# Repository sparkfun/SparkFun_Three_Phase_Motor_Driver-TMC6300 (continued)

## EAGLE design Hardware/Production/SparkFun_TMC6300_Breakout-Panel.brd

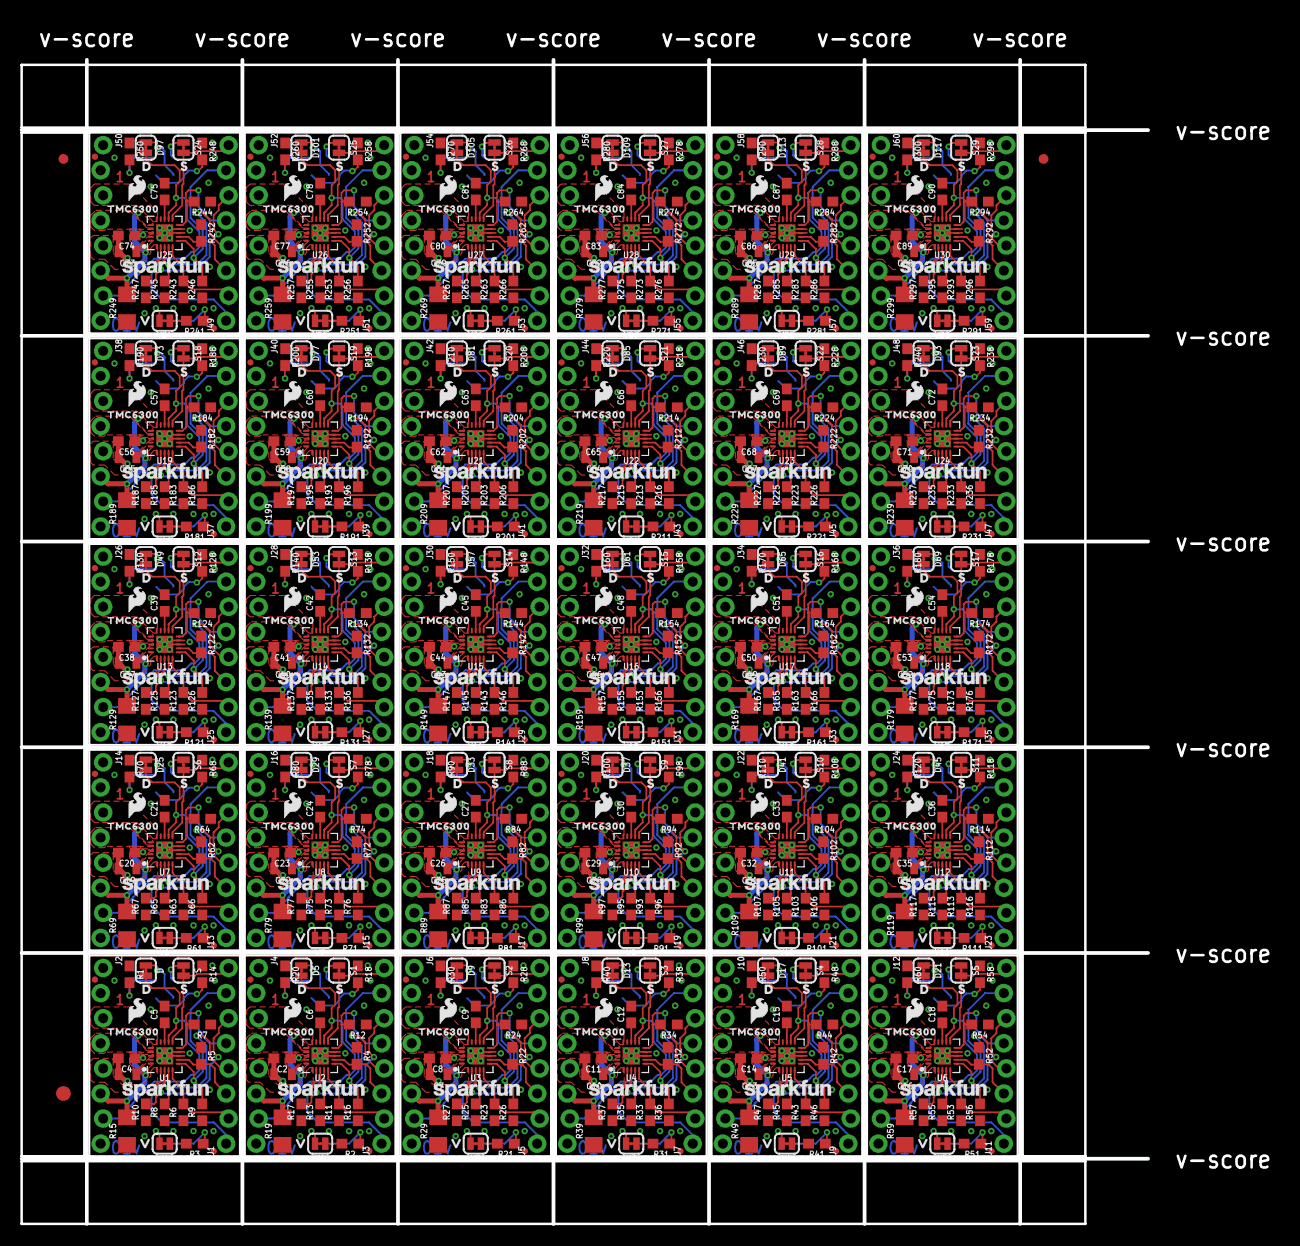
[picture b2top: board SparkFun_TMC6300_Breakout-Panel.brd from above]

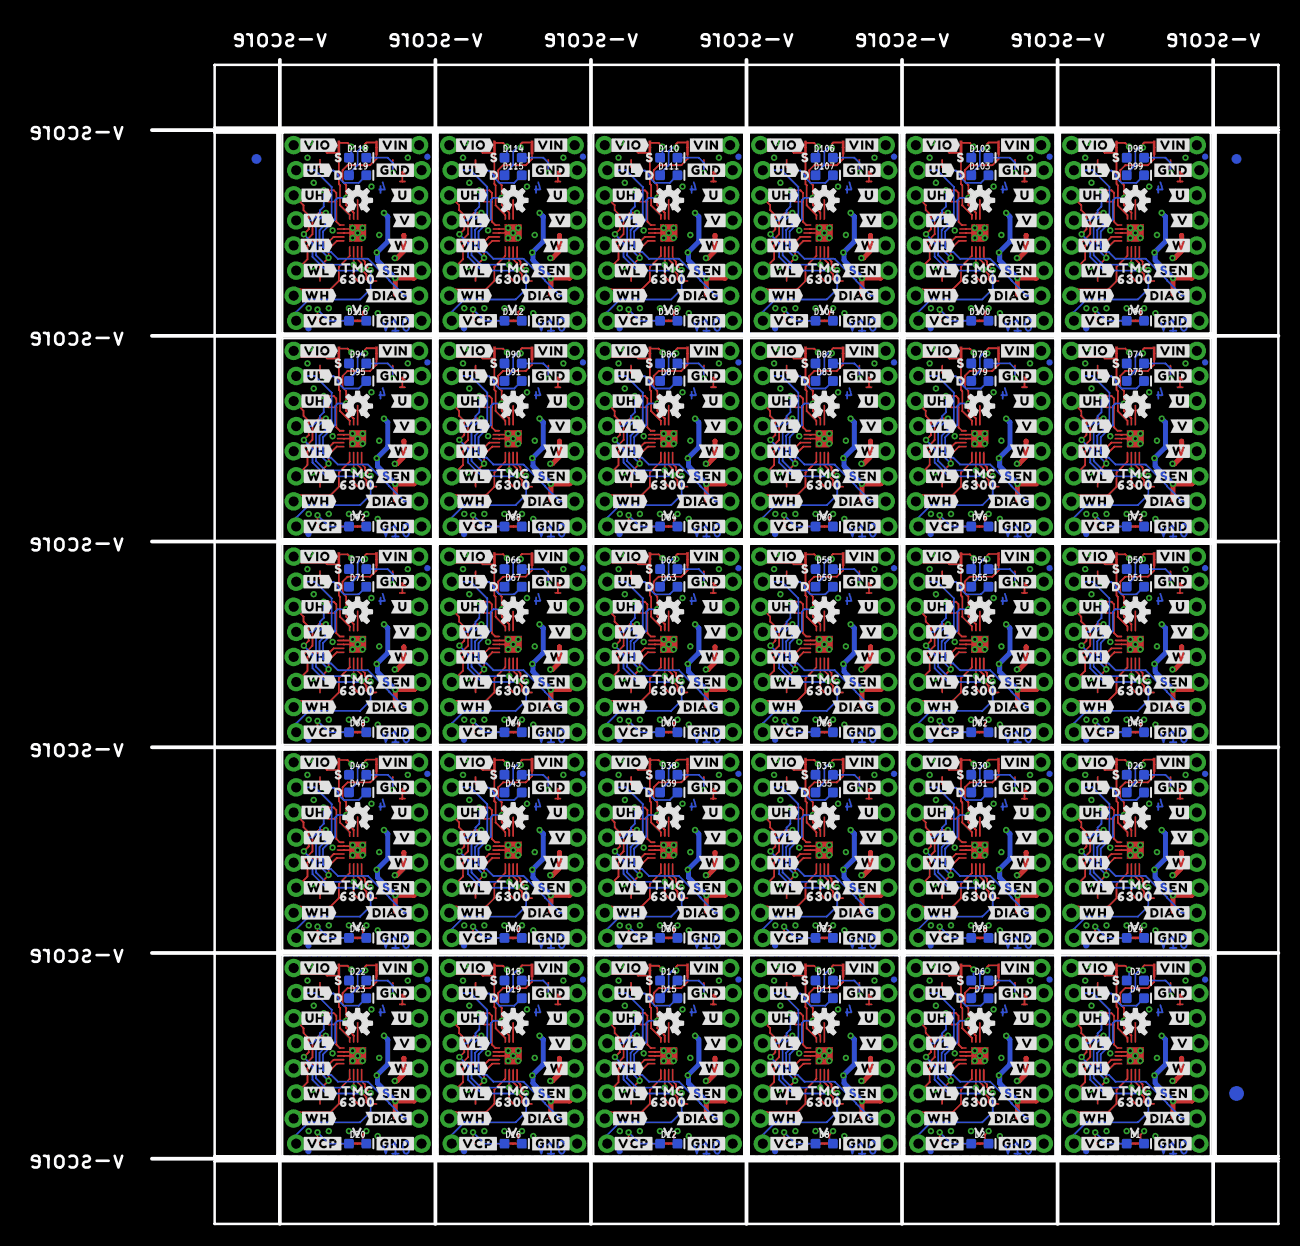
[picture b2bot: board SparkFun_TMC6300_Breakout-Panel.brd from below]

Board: 4 copper layers, 114.0 x 117.9 mm, 1626 parts (813 on the bottom side), 660 nets.

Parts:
C1, C3, C7, C10, C13, C16, C19, C22, C25, C28, C31, C34, C37, C40, C43, C46, C49, C52, C55, C58, C61, C64, C67, C70, C73, C76, C79, C82, C85, C88: 10uF; 0805
C2, C4, C5, C6, C8, C9, C11, C12, C14, C15, C17, C18, C20, C21, C23, C24, C26, C27, C29, C30, C32, C33, C35, C36, C38, C39, C41, C42, C44, C45, C47, C48, C50, C51, C53, C54, C56, C57, C59, C60, C62, C63, C65, C66, C68, C69, C71, C72, C74, C75, C77, C78, C80, C81, C83, C84, C86, C87, C89, C90: 0.1uF; 0603
D, D5, D9, D13, D17, D21, D25, D29, D33, D37, D41, D45, D49, D53, D57, D61, D65, D69, D73, D77, D81, D85, D89, D93, D97, D101, D105, D109, D113, D117: JUMPER-SMT_2_NC_TRACE_SILK; SMT-JUMPER_2_NC_TRACE_SILK
D1, D2, D8, D12, D16, D20, D24, D28, D32, D36, D40, D44, D48, D52, D56, D60, D64, D68, D72, D76, D80, D84, D88, D92, D96, D100, D104, D108, D112, D116: RED; LED-0603
D3, D6, D10, D14, D18, D22, D26, D30, D34, D38, D42, D46, D50, D54, D58, D62, D66, D70, D74, D78, D82, D86, D90, D94, D98, D102, D106, D110, D114, D118: BLUE; LED-0603
D4, D7, D11, D15, D19, D23, D27, D31, D35, D39, D43, D47, D51, D55, D59, D63, D67, D71, D75, D79, D83, D87, D91, D95, D99, D103, D107, D111, D115, D119: GREEN; LED-0603
E$1, E$2, E$3, E$4: FIDUCIAL-1X2
E$5, E$6: FIDUCIAL-1.5X3
FD1, FD2, FD3, FD4, FD5, FD6, FD7, FD8, FD9, FD10, FD11, FD12, FD13, FD14, FD15, FD16, FD17, FD18, FD19, FD20, FD21, FD22, FD23, FD24, FD25, FD26, FD27, FD28, FD29, FD30, FD31, FD32, FD33, FD34, FD35, FD36, FD37, FD38, FD39, FD40, FD41, FD42, FD43, FD44, FD45, FD46, FD47, FD48, FD49, FD50, FD51, FD52, FD53, FD54, FD55, FD56, FD57, FD58, FD59, FD60, FD61, FD62, FD63, FD64, FD65, FD66, FD67, FD68, FD69, FD70, FD71, FD72, FD73, FD74, FD75, FD76, FD77, FD78, FD79, FD80, FD81, FD82, FD83, FD84, FD85, FD86, FD87, FD88, FD89, FD90, FD91, FD92, FD93, FD94, FD95, FD96, FD97, FD98, FD99, FD100, FD101, FD102, FD103, FD104, FD105, FD106, FD107, FD108, FD109, FD110, FD111, FD112, FD113, FD114, FD115, FD116, FD117, FD118, FD119, FD120: FIDUCIALUFIDUCIAL; FIDUCIAL-MICRO
J1, J2, J3, J4, J5, J6, J7, J8, J9, J10, J11, J12, J13, J14, J15, J16, J17, J18, J19, J20, J21, J22, J23, J24, J25, J26, J27, J28, J29, J30, J31, J32, J33, J34, J35, J36, J37, J38, J39, J40, J41, J42, J43, J44, J45, J46, J47, J48, J49, J50, J51, J52, J53, J54, J55, J56, J57, J58, J59, J60: 1X08_LOCK_NO_SILK
LOGO1, LOGO3, LOGO7, LOGO10, LOGO13, LOGO16, LOGO19, LOGO22, LOGO25, LOGO28, LOGO31, LOGO34, LOGO37, LOGO40, LOGO43, LOGO46, LOGO49, LOGO52, LOGO55, LOGO58, LOGO61, LOGO64, LOGO67, LOGO70, LOGO73, LOGO76, LOGO79, LOGO82, LOGO85, LOGO88: SFE_LOGO_NAME.08_INCH; SFE_LOGO_NAME_.08
LOGO2, LOGO4, LOGO8, LOGO11, LOGO14, LOGO17, LOGO20, LOGO23, LOGO26, LOGO29, LOGO32, LOGO35, LOGO38, LOGO41, LOGO44, LOGO47, LOGO50, LOGO53, LOGO56, LOGO59, LOGO62, LOGO65, LOGO68, LOGO71, LOGO74, LOGO77, LOGO80, LOGO83, LOGO86, LOGO89: SFE_LOGO_FLAME.1_INCH; SFE_LOGO_FLAME_.1
LOGO5, LOGO6, LOGO9, LOGO12, LOGO15, LOGO18, LOGO21, LOGO24, LOGO27, LOGO30, LOGO33, LOGO36, LOGO39, LOGO42, LOGO45, LOGO48, LOGO51, LOGO54, LOGO57, LOGO60, LOGO63, LOGO66, LOGO69, LOGO72, LOGO75, LOGO78, LOGO81, LOGO84, LOGO87, LOGO90: OSHW-LOGOS; OSHW-LOGO-S
R1, R20, R30, R40, R50, R60, R70, R80, R90, R100, R110, R120, R130, R140, R150, R160, R170, R180, R190, R200, R210, R220, R230, R240, R250, R260, R270, R280, R290, R300: 2.2k; 0603
R2, R3, R21, R31, R41, R51, R61, R71, R81, R91, R101, R111, R121, R131, R141, R151, R161, R171, R181, R191, R201, R211, R221, R231, R241, R251, R261, R271, R281, R291: 1k; 0603
R4, R5, R6, R7, R8, R9, R10, R11, R12, R13, R16, R17, R22, R23, R24, R25, R26, R27, R32, R33, R34, R35, R36, R37, R42, R43, R44, R45, R46, R47, R52, R53, R54, R55, R56, R57, R62, R63, R64, R65, R66, R67, R72, R73, R74, R75, R76, R77, R82, R83, R84, R85, R86, R87, R92, R93, R94, R95, R96, R97, R102, R103, R104, R105, R106, R107, R112, R113, R114, R115, R116, R117, R122, R123, R124, R125, R126, R127, R132, R133, R134, R135, R136, R137, R142, R143, R144, R145, R146, R147, R152, R153, R154, R155, R156, R157, R162, R163, R164, R165, R166, R167, R172, R173, R174, R175, R176, R177, R182, R183, R184, R185, R186, R187, R192, R193, R194, R195, R196, R197, R202, R203, R204, R205, R206, R207, R212, R213, R214, R215, R216, R217, R222, R223, R224, R225, R226, R227, R232, R233, R234, R235, R236, R237, R242, R243, R244, R245, R246, R247, R252, R253, R254, R255, R256, R257, R262, R263, R264, R265, R266, R267, R272, R273, R274, R275, R276, R277, R282, R283, R284, R285, R286, R287, R292, R293, R294, R295, R296, R297: 100k; 0603
R14, R18, R28, R38, R48, R58, R68, R78, R88, R98, R108, R118, R128, R138, R148, R158, R168, R178, R188, R198, R208, R218, R228, R238, R248, R258, R268, R278, R288, R298: 330; 0603
R15, R19, R29, R39, R49, R59, R69, R79, R89, R99, R109, R119, R129, R139, R149, R159, R169, R179, R189, R199, R209, R219, R229, R239, R249, R259, R269, R279, R289, R299: 0.12; 1206
S, S1, S2, S3, S4, S5, S6, S7, S8, S9, S10, S11, S12, S13, S14, S15, S16, S17, S18, S19, S20, S21, S22, S23, S24, S25, S26, S27, S28, S29: JUMPER-SMT_2_NC_TRACE_SILK; SMT-JUMPER_2_NC_TRACE_SILK
U1, U2, U3, U4, U5, U6, U7, U8, U9, U10, U11, U12, U13, U14, U15, U16, U17, U18, U19, U20, U21, U22, U23, U24, U25, U26, U27, U28, U29, U30: TMC6300; QFN-20
U$1, U$5, U$28, U$38, U$51, U$63, U$76, U$88, U$101, U$113, U$126, U$138, U$151, U$163, U$176, U$188, U$201, U$213, U$226, U$238, U$251, U$263, U$276, U$288, U$301, U$313, U$326, U$338, U$351, U$363, U$376, U$388, U$401, U$413, U$426, U$438, U$451, U$463, U$476, U$488, U$501, U$513, U$526, U$538, U$551, U$563, U$576, U$588, U$601, U$613, U$626, U$638, U$651, U$663, U$676, U$688, U$701, U$713, U$726, U$738: #GND#1
U$2, U$48, U$73, U$98, U$123, U$148, U$173, U$198, U$223, U$248, U$273, U$298, U$323, U$348, U$373, U$398, U$423, U$448, U$473, U$498, U$523, U$548, U$573, U$598, U$623, U$648, U$673, U$698, U$723, U$748: #SEN#0
U$3, U$49, U$74, U$99, U$124, U$149, U$174, U$199, U$224, U$249, U$274, U$299, U$324, U$349, U$374, U$399, U$424, U$449, U$474, U$499, U$524, U$549, U$574, U$599, U$624, U$649, U$674, U$699, U$724, U$749: #DIAG#0
U$4, U$50, U$75, U$100, U$125, U$150, U$175, U$200, U$225, U$250, U$275, U$300, U$325, U$350, U$375, U$400, U$425, U$450, U$475, U$500, U$525, U$550, U$575, U$600, U$625, U$650, U$675, U$700, U$725, U$750: TMC630063003454
U$6, U$12, U$52, U$77, U$102, U$127, U$152, U$177, U$202, U$227, U$252, U$277, U$302, U$327, U$352, U$377, U$402, U$427, U$452, U$477, U$502, U$527, U$552, U$577, U$602, U$627, U$652, U$677, U$702, U$727: #VCP#0
U$7, U$13, U$53, U$78, U$103, U$128, U$153, U$178, U$203, U$228, U$253, U$278, U$303, U$328, U$353, U$378, U$403, U$428, U$453, U$478, U$503, U$528, U$553, U$578, U$603, U$628, U$653, U$678, U$703, U$728: #VIO#1
U$8, U$14, U$16, U$18, U$54, U$57, U$79, U$82, U$104, U$107, U$129, U$132, U$154, U$157, U$179, U$182, U$204, U$207, U$229, U$232, U$254, U$257, U$279, U$282, U$304, U$307, U$329, U$332, U$354, U$357, U$379, U$382, U$404, U$407, U$429, U$432, U$454, U$457, U$479, U$482, U$504, U$507, U$529, U$532, U$554, U$557, U$579, U$582, U$604, U$607, U$629, U$632, U$654, U$657, U$679, U$682, U$704, U$707, U$729, U$732: D0
U$9, U$39, U$64, U$89, U$114, U$139, U$164, U$189, U$214, U$239, U$264, U$289, U$314, U$339, U$364, U$389, U$414, U$439, U$464, U$489, U$514, U$539, U$564, U$589, U$614, U$639, U$664, U$689, U$714, U$739: #U#6
U$10, U$20, U$26, U$29, U$55, U$59, U$80, U$84, U$105, U$109, U$130, U$134, U$155, U$159, U$180, U$184, U$205, U$209, U$230, U$234, U$255, U$259, U$280, U$284, U$305, U$309, U$330, U$334, U$355, U$359, U$380, U$384, U$405, U$409, U$430, U$434, U$455, U$459, U$480, U$484, U$505, U$509, U$530, U$534, U$555, U$559, U$580, U$584, U$605, U$609, U$630, U$634, U$655, U$659, U$680, U$684, U$705, U$709, U$730, U$734: V2
U$11, U$17, U$19, U$27, U$56, U$58, U$81, U$83, U$106, U$108, U$131, U$133, U$156, U$158, U$181, U$183, U$206, U$208, U$231, U$233, U$256, U$258, U$281, U$283, U$306, U$308, U$331, U$333, U$356, U$358, U$381, U$383, U$406, U$408, U$431, U$433, U$456, U$458, U$481, U$483, U$506, U$508, U$531, U$533, U$556, U$558, U$581, U$583, U$606, U$608, U$631, U$633, U$656, U$658, U$681, U$683, U$706, U$708, U$731, U$733: S1
U$15, U$35, U$60, U$85, U$110, U$135, U$160, U$185, U$210, U$235, U$260, U$285, U$310, U$335, U$360, U$385, U$410, U$435, U$460, U$485, U$510, U$535, U$560, U$585, U$610, U$635, U$660, U$685, U$710, U$735: 63001
U$21, U$40, U$65, U$90, U$115, U$140, U$165, U$190, U$215, U$240, U$265, U$290, U$315, U$340, U$365, U$390, U$415, U$440, U$465, U$490, U$515, U$540, U$565, U$590, U$615, U$640, U$665, U$690, U$715, U$740: #UH#5
U$22, U$41, U$66, U$91, U$116, U$141, U$166, U$191, U$216, U$241, U$266, U$291, U$316, U$341, U$366, U$391, U$416, U$441, U$466, U$491, U$516, U$541, U$566, U$591, U$616, U$641, U$666, U$691, U$716, U$741: #UL#4
U$23, U$36, U$61, U$86, U$111, U$136, U$161, U$186, U$211, U$236, U$261, U$286, U$311, U$336, U$361, U$386, U$411, U$436, U$461, U$486, U$511, U$536, U$561, U$586, U$611, U$636, U$661, U$686, U$711, U$736: TMC0
U$24, U$37, U$62, U$87, U$112, U$137, U$162, U$187, U$212, U$237, U$262, U$287, U$312, U$337, U$362, U$387, U$412, U$437, U$462, U$487, U$512, U$537, U$562, U$587, U$612, U$637, U$662, U$687, U$712, U$737: #VIN#0
U$25, U$42, U$67, U$92, U$117, U$142, U$167, U$192, U$217, U$242, U$267, U$292, U$317, U$342, U$367, U$392, U$417, U$442, U$467, U$492, U$517, U$542, U$567, U$592, U$617, U$642, U$667, U$692, U$717, U$742: #V#7
U$30, U$43, U$68, U$93, U$118, U$143, U$168, U$193, U$218, U$243, U$268, U$293, U$318, U$343, U$368, U$393, U$418, U$443, U$468, U$493, U$518, U$543, U$568, U$593, U$618, U$643, U$668, U$693, U$718, U$743: #VH#2
U$31, U$44, U$69, U$94, U$119, U$144, U$169, U$194, U$219, U$244, U$269, U$294, U$319, U$344, U$369, U$394, U$419, U$444, U$469, U$494, U$519, U$544, U$569, U$594, U$619, U$644, U$669, U$694, U$719, U$744: #VL#3
U$32, U$45, U$70, U$95, U$120, U$145, U$170, U$195, U$220, U$245, U$270, U$295, U$320, U$345, U$370, U$395, U$420, U$445, U$470, U$495, U$520, U$545, U$570, U$595, U$620, U$645, U$670, U$695, U$720, U$745: #W#8
U$33, U$46, U$71, U$96, U$121, U$146, U$171, U$196, U$221, U$246, U$271, U$296, U$321, U$346, U$371, U$396, U$421, U$446, U$471, U$496, U$521, U$546, U$571, U$596, U$621, U$646, U$671, U$696, U$721, U$746: #WH#1
U$34, U$47, U$72, U$97, U$122, U$147, U$172, U$197, U$222, U$247, U$272, U$297, U$322, U$347, U$372, U$397, U$422, U$447, U$472, U$497, U$522, U$547, U$572, U$597, U$622, U$647, U$672, U$697, U$722, U$747: #WL#0
V, V1, V2, V3, V4, V5, V6, V7, V8, V9, V10, V11, V12, V13, V14, V15, V16, V17, V18, V19, V20, V21, V22, V23, V24, V25, V26, V27, V28, V29: JUMPER-SMT_2_NC_TRACE_SILK; SMT-JUMPER_2_NC_TRACE_SILK

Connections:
DIAG: D.2, J2.7, U1.12
DIAG1: D5.2, J4.7, U2.12
DIAG2: D9.2, J6.7, U3.12
DIAG3: D13.2, J8.7, U4.12
DIAG4: D17.2, J10.7, U5.12
DIAG5: D21.2, J12.7, U6.12
DIAG6: D25.2, J14.7, U7.12
DIAG7: D29.2, J16.7, U8.12
DIAG8: D33.2, J18.7, U9.12
DIAG9: D37.2, J20.7, U10.12
DIAG10: D41.2, J22.7, U11.12
DIAG11: D45.2, J24.7, U12.12
DIAG12: D49.2, J26.7, U13.12
DIAG13: D53.2, J28.7, U14.12
DIAG14: D57.2, J30.7, U15.12
DIAG15: D61.2, J32.7, U16.12
DIAG16: D65.2, J34.7, U17.12
DIAG17: D69.2, J36.7, U18.12
DIAG18: D73.2, J38.7, U19.12
DIAG19: D77.2, J40.7, U20.12
DIAG20: D81.2, J42.7, U21.12
DIAG21: D85.2, J44.7, U22.12
DIAG22: D89.2, J46.7, U23.12
DIAG23: D93.2, J48.7, U24.12
DIAG24: D97.2, J50.7, U25.12
DIAG25: D101.2, J52.7, U26.12
DIAG26: D105.2, J54.7, U27.12
DIAG27: D109.2, J56.7, U28.12
DIAG28: D113.2, J58.7, U29.12
DIAG29: D117.2, J60.7, U30.12
GND: C3.2, C4.2, C5.2, D1.C, J2.2, J2.8, R1.1, R5.1, R6.1, R7.1, R8.1, R9.1, R10.1, R14.1, R15.1, U1.8, U1.9, U1.14, U1.PAD
GND1: C1.2, C2.2, C6.2, D2.C, J4.2, J4.8, R4.1, R11.1, R12.1, R13.1, R16.1, R17.1, R18.1, R19.1, R20.1, U2.8, U2.9, U2.14, U2.PAD
GND2: C7.2, C8.2, C9.2, D8.C, J6.2, J6.8, R22.1, R23.1, R24.1, R25.1, R26.1, R27.1, R28.1, R29.1, R30.1, U3.8, U3.9, U3.14, U3.PAD
GND3: C10.2, C11.2, C12.2, D12.C, J8.2, J8.8, R32.1, R33.1, R34.1, R35.1, R36.1, R37.1, R38.1, R39.1, R40.1, U4.8, U4.9, U4.14, U4.PAD
GND4: C13.2, C14.2, C15.2, D16.C, J10.2, J10.8, R42.1, R43.1, R44.1, R45.1, R46.1, R47.1, R48.1, R49.1, R50.1, U5.8, U5.9, U5.14, U5.PAD
GND5: C16.2, C17.2, C18.2, D20.C, J12.2, J12.8, R52.1, R53.1, R54.1, R55.1, R56.1, R57.1, R58.1, R59.1, R60.1, U6.8, U6.9, U6.14, U6.PAD
GND6: C19.2, C20.2, C21.2, D24.C, J14.2, J14.8, R62.1, R63.1, R64.1, R65.1, R66.1, R67.1, R68.1, R69.1, R70.1, U7.8, U7.9, U7.14, U7.PAD
GND7: C22.2, C23.2, C24.2, D28.C, J16.2, J16.8, R72.1, R73.1, R74.1, R75.1, R76.1, R77.1, R78.1, R79.1, R80.1, U8.8, U8.9, U8.14, U8.PAD
GND8: C25.2, C26.2, C27.2, D32.C, J18.2, J18.8, R82.1, R83.1, R84.1, R85.1, R86.1, R87.1, R88.1, R89.1, R90.1, U9.8, U9.9, U9.14, U9.PAD
GND9: C28.2, C29.2, C30.2, D36.C, J20.2, J20.8, R92.1, R93.1, R94.1, R95.1, R96.1, R97.1, R98.1, R99.1, R100.1, U10.8, U10.9, U10.14, U10.PAD
GND10: C31.2, C32.2, C33.2, D40.C, J22.2, J22.8, R102.1, R103.1, R104.1, R105.1, R106.1, R107.1, R108.1, R109.1, R110.1, U11.8, U11.9, U11.14, U11.PAD
GND11: C34.2, C35.2, C36.2, D44.C, J24.2, J24.8, R112.1, R113.1, R114.1, R115.1, R116.1, R117.1, R118.1, R119.1, R120.1, U12.8, U12.9, U12.14, U12.PAD
GND12: C37.2, C38.2, C39.2, D48.C, J26.2, J26.8, R122.1, R123.1, R124.1, R125.1, R126.1, R127.1, R128.1, R129.1, R130.1, U13.8, U13.9, U13.14, U13.PAD
GND13: C40.2, C41.2, C42.2, D52.C, J28.2, J28.8, R132.1, R133.1, R134.1, R135.1, R136.1, R137.1, R138.1, R139.1, R140.1, U14.8, U14.9, U14.14, U14.PAD
GND14: C43.2, C44.2, C45.2, D56.C, J30.2, J30.8, R142.1, R143.1, R144.1, R145.1, R146.1, R147.1, R148.1, R149.1, R150.1, U15.8, U15.9, U15.14, U15.PAD
GND15: C46.2, C47.2, C48.2, D60.C, J32.2, J32.8, R152.1, R153.1, R154.1, R155.1, R156.1, R157.1, R158.1, R159.1, R160.1, U16.8, U16.9, U16.14, U16.PAD
GND16: C49.2, C50.2, C51.2, D64.C, J34.2, J34.8, R162.1, R163.1, R164.1, R165.1, R166.1, R167.1, R168.1, R169.1, R170.1, U17.8, U17.9, U17.14, U17.PAD
GND17: C52.2, C53.2, C54.2, D68.C, J36.2, J36.8, R172.1, R173.1, R174.1, R175.1, R176.1, R177.1, R178.1, R179.1, R180.1, U18.8, U18.9, U18.14, U18.PAD
GND18: C55.2, C56.2, C57.2, D72.C, J38.2, J38.8, R182.1, R183.1, R184.1, R185.1, R186.1, R187.1, R188.1, R189.1, R190.1, U19.8, U19.9, U19.14, U19.PAD
GND19: C58.2, C59.2, C60.2, D76.C, J40.2, J40.8, R192.1, R193.1, R194.1, R195.1, R196.1, R197.1, R198.1, R199.1, R200.1, U20.8, U20.9, U20.14, U20.PAD
GND20: C61.2, C62.2, C63.2, D80.C, J42.2, J42.8, R202.1, R203.1, R204.1, R205.1, R206.1, R207.1, R208.1, R209.1, R210.1, U21.8, U21.9, U21.14, U21.PAD
GND21: C64.2, C65.2, C66.2, D84.C, J44.2, J44.8, R212.1, R213.1, R214.1, R215.1, R216.1, R217.1, R218.1, R219.1, R220.1, U22.8, U22.9, U22.14, U22.PAD
GND22: C67.2, C68.2, C69.2, D88.C, J46.2, J46.8, R222.1, R223.1, R224.1, R225.1, R226.1, R227.1, R228.1, R229.1, R230.1, U23.8, U23.9, U23.14, U23.PAD
GND23: C70.2, C71.2, C72.2, D92.C, J48.2, J48.8, R232.1, R233.1, R234.1, R235.1, R236.1, R237.1, R238.1, R239.1, R240.1, U24.8, U24.9, U24.14, U24.PAD
GND24: C73.2, C74.2, C75.2, D96.C, J50.2, J50.8, R242.1, R243.1, R244.1, R245.1, R246.1, R247.1, R248.1, R249.1, R250.1, U25.8, U25.9, U25.14, U25.PAD
GND25: C76.2, C77.2, C78.2, D100.C, J52.2, J52.8, R252.1, R253.1, R254.1, R255.1, R256.1, R257.1, R258.1, R259.1, R260.1, U26.8, U26.9, U26.14, U26.PAD
GND26: C79.2, C80.2, C81.2, D104.C, J54.2, J54.8, R262.1, R263.1, R264.1, R265.1, R266.1, R267.1, R268.1, R269.1, R270.1, U27.8, U27.9, U27.14, U27.PAD
GND27: C82.2, C83.2, C84.2, D108.C, J56.2, J56.8, R272.1, R273.1, R274.1, R275.1, R276.1, R277.1, R278.1, R279.1, R280.1, U28.8, U28.9, U28.14, U28.PAD
GND28: C85.2, C86.2, C87.2, D112.C, J58.2, J58.8, R282.1, R283.1, R284.1, R285.1, R286.1, R287.1, R288.1, R289.1, R290.1, U29.8, U29.9, U29.14, U29.PAD
GND29: C88.2, C89.2, C90.2, D116.C, J60.2, J60.8, R292.1, R293.1, R294.1, R295.1, R296.1, R297.1, R298.1, R299.1, R300.1, U30.8, U30.9, U30.14, U30.PAD
unnamed: R3.2, V.1
unnamed: R2.2, V1.1
unnamed: D2.A, R2.1
unnamed: D1.A, R3.1
unnamed: D3.A, S.1
unnamed: C5.1, U1.13
unnamed: C6.1, U2.13
unnamed: D5.1, D7.A
unnamed: D.1, D4.A
unnamed: D3.C, R1.2
unnamed: D6.A, S1.1
unnamed: D4.C, R14.2
unnamed: D7.C, R18.2
unnamed: D6.C, R20.2
unnamed: R21.2, V2.1
unnamed: D8.A, R21.1
unnamed: C9.1, U3.13
unnamed: D9.1, D11.A
unnamed: D10.A, S2.1
unnamed: D11.C, R28.2
unnamed: D10.C, R30.2
unnamed: R31.2, V3.1
unnamed: D12.A, R31.1
unnamed: C12.1, U4.13
unnamed: D13.1, D15.A
unnamed: D14.A, S3.1
unnamed: D15.C, R38.2
unnamed: D14.C, R40.2
unnamed: R41.2, V4.1
unnamed: D16.A, R41.1
unnamed: C15.1, U5.13
unnamed: D17.1, D19.A
unnamed: D18.A, S4.1
unnamed: D19.C, R48.2
unnamed: D18.C, R50.2
unnamed: R51.2, V5.1
unnamed: D20.A, R51.1
unnamed: C18.1, U6.13
unnamed: D21.1, D23.A
unnamed: D22.A, S5.1
unnamed: D23.C, R58.2
unnamed: D22.C, R60.2
unnamed: R61.2, V6.1
unnamed: D24.A, R61.1
unnamed: C21.1, U7.13
unnamed: D25.1, D27.A
unnamed: D26.A, S6.1
unnamed: D27.C, R68.2
unnamed: D26.C, R70.2
unnamed: R71.2, V7.1
unnamed: D28.A, R71.1
unnamed: C24.1, U8.13
unnamed: D29.1, D31.A
unnamed: D30.A, S7.1
unnamed: D31.C, R78.2
unnamed: D30.C, R80.2
unnamed: R81.2, V8.1
unnamed: D32.A, R81.1
unnamed: C27.1, U9.13
unnamed: D33.1, D35.A
unnamed: D34.A, S8.1
unnamed: D35.C, R88.2
unnamed: D34.C, R90.2
unnamed: R91.2, V9.1
unnamed: D36.A, R91.1
unnamed: C30.1, U10.13
unnamed: D37.1, D39.A
unnamed: D38.A, S9.1
unnamed: D39.C, R98.2
unnamed: D38.C, R100.2
unnamed: R101.2, V10.1
unnamed: D40.A, R101.1
unnamed: C33.1, U11.13
unnamed: D41.1, D43.A
unnamed: D42.A, S10.1
unnamed: D43.C, R108.2
unnamed: D42.C, R110.2
unnamed: R111.2, V11.1
unnamed: D44.A, R111.1
unnamed: C36.1, U12.13
unnamed: D45.1, D47.A
unnamed: D46.A, S11.1
unnamed: D47.C, R118.2
unnamed: D46.C, R120.2
unnamed: R121.2, V12.1
unnamed: D48.A, R121.1
unnamed: C39.1, U13.13
unnamed: D49.1, D51.A
unnamed: D50.A, S12.1
unnamed: D51.C, R128.2
unnamed: D50.C, R130.2
unnamed: R131.2, V13.1
unnamed: D52.A, R131.1
unnamed: C42.1, U14.13
unnamed: D53.1, D55.A
unnamed: D54.A, S13.1
unnamed: D55.C, R138.2
unnamed: D54.C, R140.2
unnamed: R141.2, V14.1
unnamed: D56.A, R141.1
unnamed: C45.1, U15.13
unnamed: D57.1, D59.A
unnamed: D58.A, S14.1
unnamed: D59.C, R148.2
unnamed: D58.C, R150.2
unnamed: R151.2, V15.1
unnamed: D60.A, R151.1
unnamed: C48.1, U16.13
unnamed: D61.1, D63.A
unnamed: D62.A, S15.1
unnamed: D63.C, R158.2
unnamed: D62.C, R160.2
unnamed: R161.2, V16.1
unnamed: D64.A, R161.1
unnamed: C51.1, U17.13
unnamed: D65.1, D67.A
unnamed: D66.A, S16.1
unnamed: D67.C, R168.2
unnamed: D66.C, R170.2
unnamed: R171.2, V17.1
unnamed: D68.A, R171.1
unnamed: C54.1, U18.13
unnamed: D69.1, D71.A
unnamed: D70.A, S17.1
unnamed: D71.C, R178.2
unnamed: D70.C, R180.2
unnamed: R181.2, V18.1
unnamed: D72.A, R181.1
unnamed: C57.1, U19.13
unnamed: D73.1, D75.A
unnamed: D74.A, S18.1
unnamed: D75.C, R188.2
unnamed: D74.C, R190.2
unnamed: R191.2, V19.1
unnamed: D76.A, R191.1
unnamed: C60.1, U20.13
unnamed: D77.1, D79.A
unnamed: D78.A, S19.1
unnamed: D79.C, R198.2
unnamed: D78.C, R200.2
unnamed: R201.2, V20.1
unnamed: D80.A, R201.1
unnamed: C63.1, U21.13
unnamed: D81.1, D83.A
unnamed: D82.A, S20.1
unnamed: D83.C, R208.2
unnamed: D82.C, R210.2
unnamed: R211.2, V21.1
unnamed: D84.A, R211.1
unnamed: C66.1, U22.13
unnamed: D85.1, D87.A
unnamed: D86.A, S21.1
unnamed: D87.C, R218.2
unnamed: D86.C, R220.2
unnamed: R221.2, V22.1
unnamed: D88.A, R221.1
unnamed: C69.1, U23.13
unnamed: D89.1, D91.A
unnamed: D90.A, S22.1
unnamed: D91.C, R228.2
unnamed: D90.C, R230.2
unnamed: R231.2, V23.1
unnamed: D92.A, R231.1
unnamed: C72.1, U24.13
unnamed: D93.1, D95.A
unnamed: D94.A, S23.1
unnamed: D95.C, R238.2
unnamed: D94.C, R240.2
unnamed: R241.2, V24.1
unnamed: D96.A, R241.1
unnamed: C75.1, U25.13
unnamed: D97.1, D99.A
unnamed: D98.A, S24.1
unnamed: D99.C, R248.2
unnamed: D98.C, R250.2
unnamed: R251.2, V25.1
unnamed: D100.A, R251.1
unnamed: C78.1, U26.13
unnamed: D101.1, D103.A
unnamed: D102.A, S25.1
unnamed: D103.C, R258.2
unnamed: D102.C, R260.2
unnamed: R261.2, V26.1
unnamed: D104.A, R261.1
unnamed: C81.1, U27.13
unnamed: D105.1, D107.A
unnamed: D106.A, S26.1
unnamed: D107.C, R268.2
unnamed: D106.C, R270.2
unnamed: R271.2, V27.1
unnamed: D108.A, R271.1
unnamed: C84.1, U28.13
unnamed: D109.1, D111.A
unnamed: D110.A, S27.1
unnamed: D111.C, R278.2
unnamed: D110.C, R280.2
unnamed: R281.2, V28.1
unnamed: D112.A, R281.1
unnamed: C87.1, U29.13
unnamed: D113.1, D115.A
unnamed: D114.A, S28.1
unnamed: D115.C, R288.2
unnamed: D114.C, R290.2
unnamed: R291.2, V29.1
unnamed: D116.A, R291.1
unnamed: C90.1, U30.13
unnamed: D117.1, D119.A
unnamed: D118.A, S29.1
unnamed: D119.C, R298.2
unnamed: D118.C, R300.2
SENSE: J2.6, R15.2, U1.16, U1.20
SENSE1: J4.6, R19.2, U2.16, U2.20
SENSE2: J6.6, R29.2, U3.16, U3.20
SENSE3: J8.6, R39.2, U4.16, U4.20
SENSE4: J10.6, R49.2, U5.16, U5.20
SENSE5: J12.6, R59.2, U6.16, U6.20
SENSE6: J14.6, R69.2, U7.16, U7.20
SENSE7: J16.6, R79.2, U8.16, U8.20
SENSE8: J18.6, R89.2, U9.16, U9.20
SENSE9: J20.6, R99.2, U10.16, U10.20
SENSE10: J22.6, R109.2, U11.16, U11.20
SENSE11: J24.6, R119.2, U12.16, U12.20
SENSE12: J26.6, R129.2, U13.16, U13.20
SENSE13: J28.6, R139.2, U14.16, U14.20
SENSE14: J30.6, R149.2, U15.16, U15.20
SENSE15: J32.6, R159.2, U16.16, U16.20
SENSE16: J34.6, R169.2, U17.16, U17.20
SENSE17: J36.6, R179.2, U18.16, U18.20
SENSE18: J38.6, R189.2, U19.16, U19.20
SENSE19: J40.6, R199.2, U20.16, U20.20
SENSE20: J42.6, R209.2, U21.16, U21.20
SENSE21: J44.6, R219.2, U22.16, U22.20
SENSE22: J46.6, R229.2, U23.16, U23.20
SENSE23: J48.6, R239.2, U24.16, U24.20
SENSE24: J50.6, R249.2, U25.16, U25.20
SENSE25: J52.6, R259.2, U26.16, U26.20
SENSE26: J54.6, R269.2, U27.16, U27.20
SENSE27: J56.6, R279.2, U28.16, U28.20
SENSE28: J58.6, R289.2, U29.16, U29.20
SENSE29: J60.6, R299.2, U30.16, U30.20
U: J2.3, U1.15
U1: J4.3, U2.15
U2: J6.3, U3.15
U3: J8.3, U4.15
U4: J10.3, U5.15
U5: J12.3, U6.15
U6: J14.3, U7.15
U7: J16.3, U8.15
U8: J18.3, U9.15
U9: J20.3, U10.15
U10: J22.3, U11.15
U11: J24.3, U12.15
U12: J26.3, U13.15
U13: J28.3, U14.15
U14: J30.3, U15.15
U15: J32.3, U16.15
U16: J34.3, U17.15
U17: J36.3, U18.15
U18: J38.3, U19.15
U19: J40.3, U20.15
U20: J42.3, U21.15
U21: J44.3, U22.15
U22: J46.3, U23.15
U23: J48.3, U24.15
U24: J50.3, U25.15
U25: J52.3, U26.15
U26: J54.3, U27.15
U27: J56.3, U28.15
U28: J58.3, U29.15
U29: J60.3, U30.15
UH: J1.6, R10.2, U1.3
UH1: J3.6, R17.2, U2.3
UH2: J5.6, R27.2, U3.3
UH3: J7.6, R37.2, U4.3
UH4: J9.6, R47.2, U5.3
UH5: J11.6, R57.2, U6.3
UH6: J13.6, R67.2, U7.3
UH7: J15.6, R77.2, U8.3
UH8: J17.6, R87.2, U9.3
UH9: J19.6, R97.2, U10.3
UH10: J21.6, R107.2, U11.3
UH11: J23.6, R117.2, U12.3
UH12: J25.6, R127.2, U13.3
UH13: J27.6, R137.2, U14.3
UH14: J29.6, R147.2, U15.3
UH15: J31.6, R157.2, U16.3
UH16: J33.6, R167.2, U17.3
UH17: J35.6, R177.2, U18.3
UH18: J37.6, R187.2, U19.3
UH19: J39.6, R197.2, U20.3
UH20: J41.6, R207.2, U21.3
UH21: J43.6, R217.2, U22.3
UH22: J45.6, R227.2, U23.3
UH23: J47.6, R237.2, U24.3
UH24: J49.6, R247.2, U25.3
UH25: J51.6, R257.2, U26.3
UH26: J53.6, R267.2, U27.3
UH27: J55.6, R277.2, U28.3
UH28: J57.6, R287.2, U29.3
UH29: J59.6, R297.2, U30.3
UL: J1.7, R9.2, U1.6
UL1: J3.7, R16.2, U2.6
UL2: J5.7, R26.2, U3.6
UL3: J7.7, R36.2, U4.6
UL4: J9.7, R46.2, U5.6
UL5: J11.7, R56.2, U6.6
UL6: J13.7, R66.2, U7.6
UL7: J15.7, R76.2, U8.6
UL8: J17.7, R86.2, U9.6
UL9: J19.7, R96.2, U10.6
UL10: J21.7, R106.2, U11.6
UL11: J23.7, R116.2, U12.6
UL12: J25.7, R126.2, U13.6
UL13: J27.7, R136.2, U14.6
UL14: J29.7, R146.2, U15.6
UL15: J31.7, R156.2, U16.6
UL16: J33.7, R166.2, U17.6
UL17: J35.7, R176.2, U18.6
UL18: J37.7, R186.2, U19.6
UL19: J39.7, R196.2, U20.6
UL20: J41.7, R206.2, U21.6
UL21: J43.7, R216.2, U22.6
UL22: J45.7, R226.2, U23.6
UL23: J47.7, R236.2, U24.6
UL24: J49.7, R246.2, U25.6
UL25: J51.7, R256.2, U26.6
UL26: J53.7, R266.2, U27.6
UL27: J55.7, R276.2, U28.6
UL28: J57.7, R286.2, U29.6
UL29: J59.7, R296.2, U30.6
V: J2.4, U1.17
V1: J4.4, U2.17
V2: J6.4, U3.17
V3: J8.4, U4.17
V4: J10.4, U5.17
V5: J12.4, U6.17
V6: J14.4, U7.17
V7: J16.4, U8.17
V8: J18.4, U9.17
V9: J20.4, U10.17
V10: J22.4, U11.17
V11: J24.4, U12.17
V12: J26.4, U13.17
V13: J28.4, U14.17
V14: J30.4, U15.17
V15: J32.4, U16.17
V16: J34.4, U17.17
V17: J36.4, U18.17
V18: J38.4, U19.17
V19: J40.4, U20.17
V20: J42.4, U21.17
V21: J44.4, U22.17
V22: J46.4, U23.17
V23: J48.4, U24.17
V24: J50.4, U25.17
V25: J52.4, U26.17
V26: J54.4, U27.17
V27: J56.4, U28.17
V28: J58.4, U29.17
V29: J60.4, U30.17
VCP: J1.1, U1.2
VCP1: J3.1, U2.2
VCP2: J5.1, U3.2
VCP3: J7.1, U4.2
VCP4: J9.1, U5.2
VCP5: J11.1, U6.2
VCP6: J13.1, U7.2
VCP7: J15.1, U8.2
VCP8: J17.1, U9.2
VCP9: J19.1, U10.2
VCP10: J21.1, U11.2
VCP11: J23.1, U12.2
VCP12: J25.1, U13.2
VCP13: J27.1, U14.2
VCP14: J29.1, U15.2
VCP15: J31.1, U16.2
VCP16: J33.1, U17.2
VCP17: J35.1, U18.2
VCP18: J37.1, U19.2
VCP19: J39.1, U20.2
VCP20: J41.1, U21.2
VCP21: J43.1, U22.2
VCP22: J45.1, U23.2
VCP23: J47.1, U24.2
VCP24: J49.1, U25.2
VCP25: J51.1, U26.2
VCP26: J53.1, U27.2
VCP27: J55.1, U28.2
VCP28: J57.1, U29.2
VCP29: J59.1, U30.2
VH: J1.4, R8.2, U1.4
VH1: J3.4, R13.2, U2.4
VH2: J5.4, R25.2, U3.4
VH3: J7.4, R35.2, U4.4
VH4: J9.4, R45.2, U5.4
VH5: J11.4, R55.2, U6.4
VH6: J13.4, R65.2, U7.4
VH7: J15.4, R75.2, U8.4
VH8: J17.4, R85.2, U9.4
VH9: J19.4, R95.2, U10.4
VH10: J21.4, R105.2, U11.4
VH11: J23.4, R115.2, U12.4
VH12: J25.4, R125.2, U13.4
VH13: J27.4, R135.2, U14.4
VH14: J29.4, R145.2, U15.4
VH15: J31.4, R155.2, U16.4
VH16: J33.4, R165.2, U17.4
VH17: J35.4, R175.2, U18.4
VH18: J37.4, R185.2, U19.4
VH19: J39.4, R195.2, U20.4
VH20: J41.4, R205.2, U21.4
VH21: J43.4, R215.2, U22.4
VH22: J45.4, R225.2, U23.4
VH23: J47.4, R235.2, U24.4
VH24: J49.4, R245.2, U25.4
VH25: J51.4, R255.2, U26.4
VH26: J53.4, R265.2, U27.4
VH27: J55.4, R275.2, U28.4
VH28: J57.4, R285.2, U29.4
VH29: J59.4, R295.2, U30.4
VIN: C3.1, C4.1, J2.1, U1.18, V.2
VIN1: C1.1, C2.1, J4.1, U2.18, V1.2
VIN2: C7.1, C8.1, J6.1, U3.18, V2.2
VIN3: C10.1, C11.1, J8.1, U4.18, V3.2
VIN4: C13.1, C14.1, J10.1, U5.18, V4.2
VIN5: C16.1, C17.1, J12.1, U6.18, V5.2
VIN6: C19.1, C20.1, J14.1, U7.18, V6.2
VIN7: C22.1, C23.1, J16.1, U8.18, V7.2
VIN8: C25.1, C26.1, J18.1, U9.18, V8.2
VIN9: C28.1, C29.1, J20.1, U10.18, V9.2
VIN10: C31.1, C32.1, J22.1, U11.18, V10.2
VIN11: C34.1, C35.1, J24.1, U12.18, V11.2
VIN12: C37.1, C38.1, J26.1, U13.18, V12.2
VIN13: C40.1, C41.1, J28.1, U14.18, V13.2
VIN14: C43.1, C44.1, J30.1, U15.18, V14.2
VIN15: C46.1, C47.1, J32.1, U16.18, V15.2
VIN16: C49.1, C50.1, J34.1, U17.18, V16.2
VIN17: C52.1, C53.1, J36.1, U18.18, V17.2
VIN18: C55.1, C56.1, J38.1, U19.18, V18.2
VIN19: C58.1, C59.1, J40.1, U20.18, V19.2
VIN20: C61.1, C62.1, J42.1, U21.18, V20.2
VIN21: C64.1, C65.1, J44.1, U22.18, V21.2
VIN22: C67.1, C68.1, J46.1, U23.18, V22.2
VIN23: C70.1, C71.1, J48.1, U24.18, V23.2
VIN24: C73.1, C74.1, J50.1, U25.18, V24.2
VIN25: C76.1, C77.1, J52.1, U26.18, V25.2
VIN26: C79.1, C80.1, J54.1, U27.18, V26.2
VIN27: C82.1, C83.1, J56.1, U28.18, V27.2
VIN28: C85.1, C86.1, J58.1, U29.18, V28.2
VIN29: C88.1, C89.1, J60.1, U30.18, V29.2
VIO/!STDBY!: J1.8, S.2, U1.11
VIO/!STDBY!1: J3.8, S1.2, U2.11
VIO/!STDBY!2: J5.8, S2.2, U3.11
VIO/!STDBY!3: J7.8, S3.2, U4.11
VIO/!STDBY!4: J9.8, S4.2, U5.11
VIO/!STDBY!5: J11.8, S5.2, U6.11
VIO/!STDBY!6: J13.8, S6.2, U7.11
VIO/!STDBY!7: J15.8, S7.2, U8.11
VIO/!STDBY!8: J17.8, S8.2, U9.11
VIO/!STDBY!9: J19.8, S9.2, U10.11
VIO/!STDBY!10: J21.8, S10.2, U11.11
VIO/!STDBY!11: J23.8, S11.2, U12.11
VIO/!STDBY!12: J25.8, S12.2, U13.11
VIO/!STDBY!13: J27.8, S13.2, U14.11
VIO/!STDBY!14: J29.8, S14.2, U15.11
VIO/!STDBY!15: J31.8, S15.2, U16.11
VIO/!STDBY!16: J33.8, S16.2, U17.11
VIO/!STDBY!17: J35.8, S17.2, U18.11
VIO/!STDBY!18: J37.8, S18.2, U19.11
VIO/!STDBY!19: J39.8, S19.2, U20.11
VIO/!STDBY!20: J41.8, S20.2, U21.11
VIO/!STDBY!21: J43.8, S21.2, U22.11
VIO/!STDBY!22: J45.8, S22.2, U23.11
VIO/!STDBY!23: J47.8, S23.2, U24.11
VIO/!STDBY!24: J49.8, S24.2, U25.11
VIO/!STDBY!25: J51.8, S25.2, U26.11
VIO/!STDBY!26: J53.8, S26.2, U27.11
VIO/!STDBY!27: J55.8, S27.2, U28.11
VIO/!STDBY!28: J57.8, S28.2, U29.11
VIO/!STDBY!29: J59.8, S29.2, U30.11
VL: J1.5, R7.2, U1.10
VL1: J3.5, R12.2, U2.10
VL2: J5.5, R24.2, U3.10
VL3: J7.5, R34.2, U4.10
VL4: J9.5, R44.2, U5.10
VL5: J11.5, R54.2, U6.10
VL6: J13.5, R64.2, U7.10
VL7: J15.5, R74.2, U8.10
VL8: J17.5, R84.2, U9.10
VL9: J19.5, R94.2, U10.10
VL10: J21.5, R104.2, U11.10
VL11: J23.5, R114.2, U12.10
VL12: J25.5, R124.2, U13.10
VL13: J27.5, R134.2, U14.10
VL14: J29.5, R144.2, U15.10
VL15: J31.5, R154.2, U16.10
VL16: J33.5, R164.2, U17.10
VL17: J35.5, R174.2, U18.10
VL18: J37.5, R184.2, U19.10
VL19: J39.5, R194.2, U20.10
VL20: J41.5, R204.2, U21.10
VL21: J43.5, R214.2, U22.10
VL22: J45.5, R224.2, U23.10
VL23: J47.5, R234.2, U24.10
VL24: J49.5, R244.2, U25.10
VL25: J51.5, R254.2, U26.10
VL26: J53.5, R264.2, U27.10
VL27: J55.5, R274.2, U28.10
VL28: J57.5, R284.2, U29.10
VL29: J59.5, R294.2, U30.10
W: J2.5, U1.1
W1: J4.5, U2.1
W2: J6.5, U3.1
W3: J8.5, U4.1
W4: J10.5, U5.1
W5: J12.5, U6.1
W6: J14.5, U7.1
W7: J16.5, U8.1
W8: J18.5, U9.1
W9: J20.5, U10.1
W10: J22.5, U11.1
W11: J24.5, U12.1
W12: J26.5, U13.1
W13: J28.5, U14.1
W14: J30.5, U15.1
W15: J32.5, U16.1
W16: J34.5, U17.1
W17: J36.5, U18.1
W18: J38.5, U19.1
W19: J40.5, U20.1
W20: J42.5, U21.1
W21: J44.5, U22.1
W22: J46.5, U23.1
W23: J48.5, U24.1
W24: J50.5, U25.1
W25: J52.5, U26.1
W26: J54.5, U27.1
W27: J56.5, U28.1
W28: J58.5, U29.1
W29: J60.5, U30.1
WH: J1.2, R6.2, U1.5
WH1: J3.2, R11.2, U2.5
WH2: J5.2, R23.2, U3.5
WH3: J7.2, R33.2, U4.5
WH4: J9.2, R43.2, U5.5
WH5: J11.2, R53.2, U6.5
WH6: J13.2, R63.2, U7.5
WH7: J15.2, R73.2, U8.5
WH8: J17.2, R83.2, U9.5
WH9: J19.2, R93.2, U10.5
WH10: J21.2, R103.2, U11.5
WH11: J23.2, R113.2, U12.5
WH12: J25.2, R123.2, U13.5
WH13: J27.2, R133.2, U14.5
WH14: J29.2, R143.2, U15.5
WH15: J31.2, R153.2, U16.5
WH16: J33.2, R163.2, U17.5
WH17: J35.2, R173.2, U18.5
WH18: J37.2, R183.2, U19.5
WH19: J39.2, R193.2, U20.5
WH20: J41.2, R203.2, U21.5
WH21: J43.2, R213.2, U22.5
WH22: J45.2, R223.2, U23.5
WH23: J47.2, R233.2, U24.5
WH24: J49.2, R243.2, U25.5
WH25: J51.2, R253.2, U26.5
WH26: J53.2, R263.2, U27.5
WH27: J55.2, R273.2, U28.5
WH28: J57.2, R283.2, U29.5
WH29: J59.2, R293.2, U30.5
WL: J1.3, R5.2, U1.7
WL1: J3.3, R4.2, U2.7
WL2: J5.3, R22.2, U3.7
WL3: J7.3, R32.2, U4.7
WL4: J9.3, R42.2, U5.7
WL5: J11.3, R52.2, U6.7
WL6: J13.3, R62.2, U7.7
WL7: J15.3, R72.2, U8.7
WL8: J17.3, R82.2, U9.7
WL9: J19.3, R92.2, U10.7
WL10: J21.3, R102.2, U11.7
WL11: J23.3, R112.2, U12.7
WL12: J25.3, R122.2, U13.7
WL13: J27.3, R132.2, U14.7
WL14: J29.3, R142.2, U15.7
WL15: J31.3, R152.2, U16.7
WL16: J33.3, R162.2, U17.7
WL17: J35.3, R172.2, U18.7
WL18: J37.3, R182.2, U19.7
WL19: J39.3, R192.2, U20.7
WL20: J41.3, R202.2, U21.7
WL21: J43.3, R212.2, U22.7
WL22: J45.3, R222.2, U23.7
WL23: J47.3, R232.2, U24.7
WL24: J49.3, R242.2, U25.7
WL25: J51.3, R252.2, U26.7
WL26: J53.3, R262.2, U27.7
WL27: J55.3, R272.2, U28.7
WL28: J57.3, R282.2, U29.7
WL29: J59.3, R292.2, U30.7

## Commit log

2023-02-14 Upload of initial SparkX files
    Files originally from Three_Phase_Motor_Driver-TM6300 in SparkX - no edits made yet
2023-02-16 Updates for red review
    Added SparkFun logo, updated notes in schematic for user, changed blue LED resistor value, added OSHW logo, created panel and CAM files.
2023-02-16 Changes made from design notes
    Changed vias to be all the same size, added paragraphs to S and D jumpers to explain what they're going to, added tRestrict layer to remove natural jumper between GND pads, fixed acid trap, added mor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
2023-02-17 Updates to layout as per design review notes
    Added numbers to each layer to determine which layer it is in the copper, added dimensions for length and width of location of the main IC.
2023-02-17 Updates from design review
    Changed tCream on the TMC6300 to be reduced by 5%, changed tRestrict polygon to a rectangle, adjusted C5 to match the datasheet for a good return path, adjusted some routing for less acid traps, adju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
2023-02-20 Updated production files
    Re generated panelized files for ordering from design review changes
2023-02-20 Final updates before ordering
    Adjusted GND traces from TMC6300 for better connection, added paragraph for Power LED in schematic, updated panelized files for ordering.
2023-04-17 Initial docs commit
    Initial commit for product documentation
2023-04-17 Update README.md
    Fix hyperlinks
2023-04-20 Add workflow action
    Builds GitHub page for product documentation
2023-04-25 Update stylesheet
    Update automatic video sizing parameters
2023-04-25 Add product video
2023-04-25 Update stylesheet
    Add maximum height for video player (compatibility w/ extra wide screens)
2023-04-25 Add QR code
    Add QR code for product video
2023-04-25 Update stylesheet
    Update to not display video_desc class when printing page
2023-06-16 Update hardware_overview.md
    Add current sense section
2023-08-21 Rename file
    Renamed section to follow ne standardization
2023-08-21 Fix Standardization
2023-08-21 Updates & Fixes
2023-08-21 Deployed a9f7c1b with MkDocs version: 1.5.2
2024-06-06 Update LICENSE.md
    Remove carriage returns
    Fix link
2025-01-08 Fix link
2025-01-08 Update workflow
2025-01-08 Deployed b1b6b2d with MkDocs version: 1.6.1
2025-02-20 Update introduction.md
    Fixing missing image
2025-02-20 Deployed ce2106a with MkDocs version: 1.6.1
2026-06-03 Deployed f433cc1 with MkDocs version: 1.6.1
